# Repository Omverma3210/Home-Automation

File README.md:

# Home-Automation
A smart home automation switch based on triac

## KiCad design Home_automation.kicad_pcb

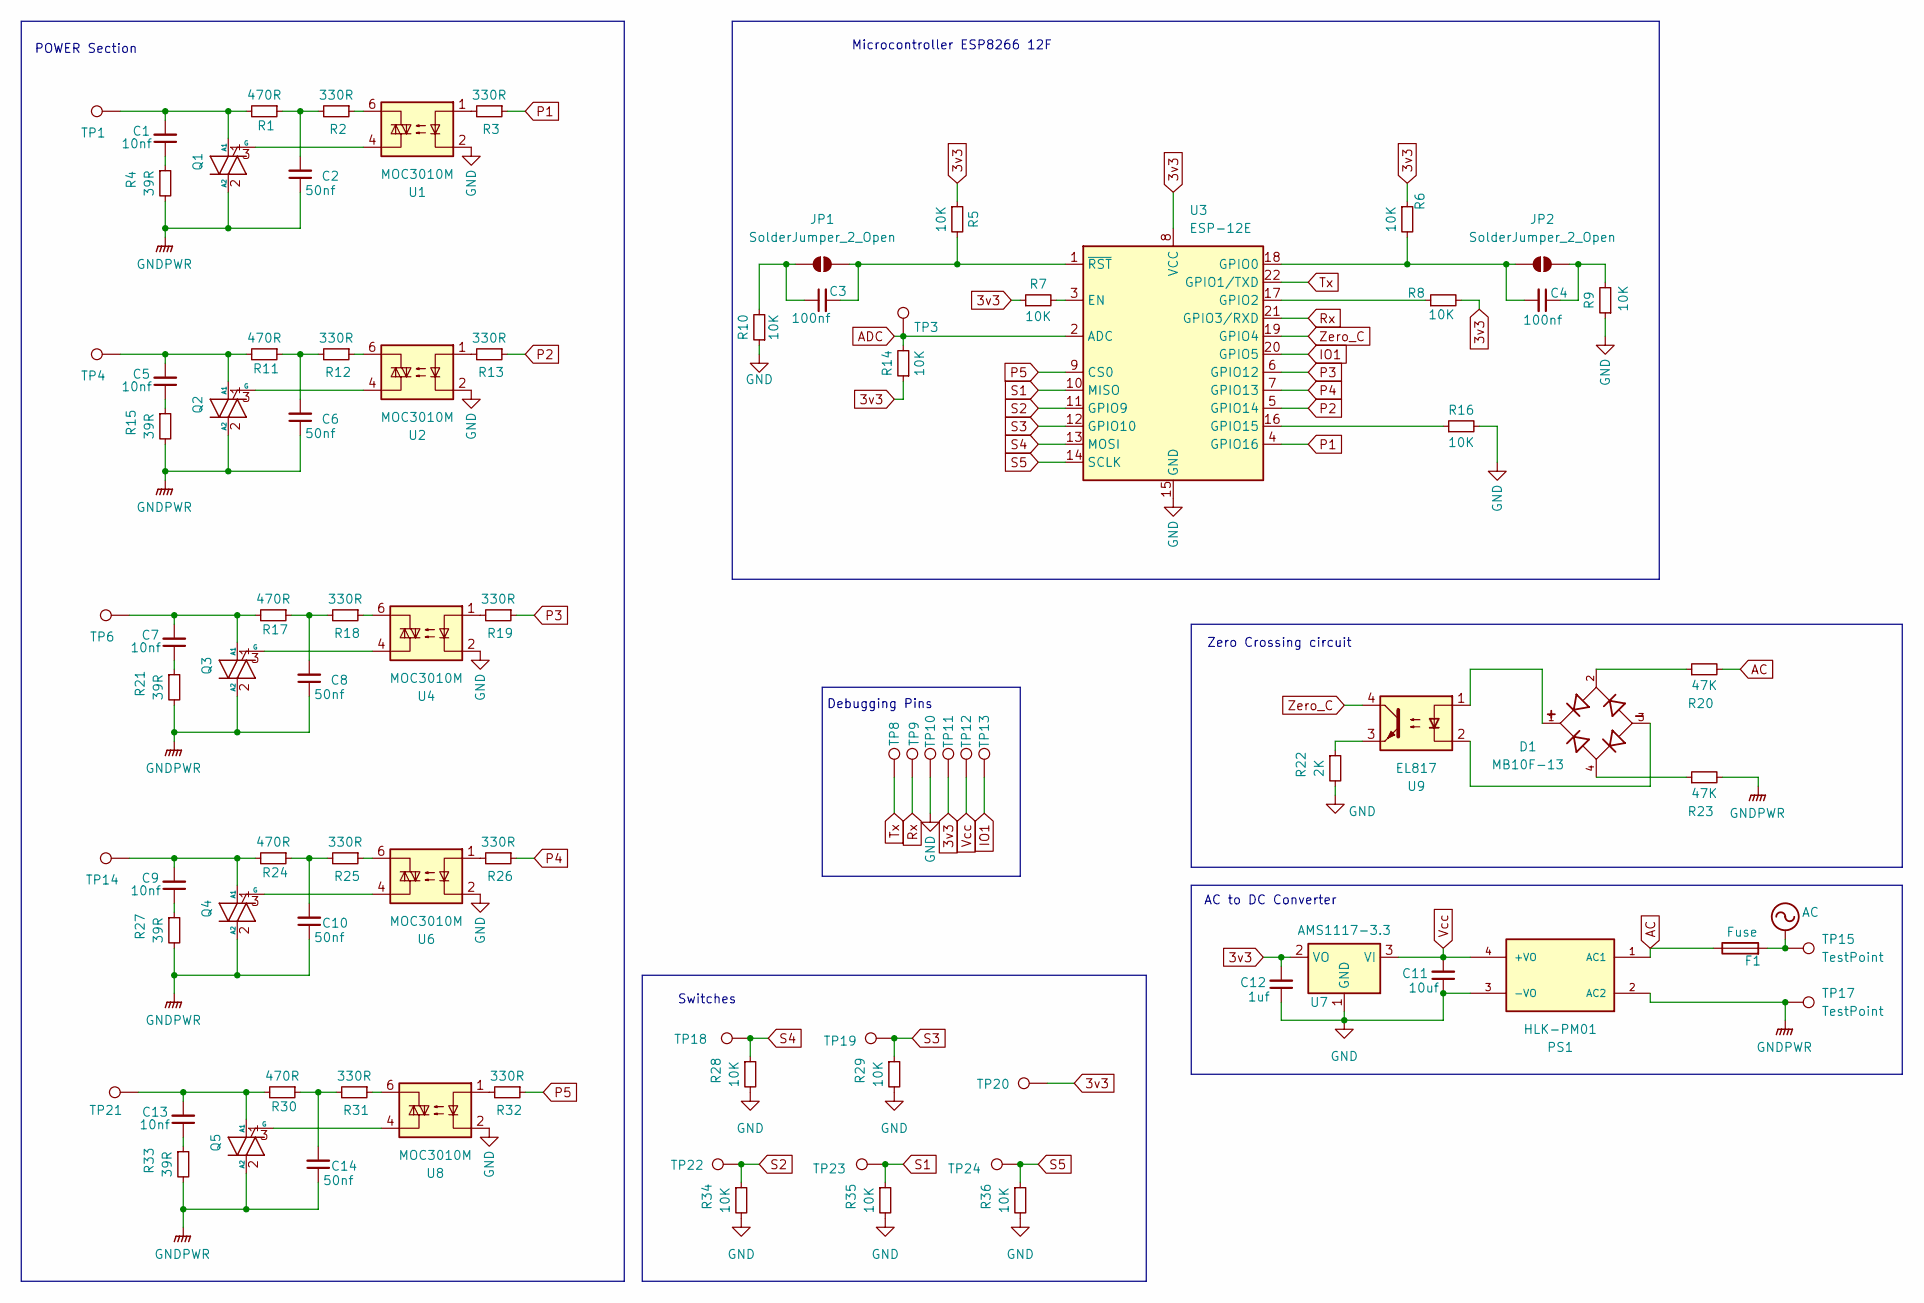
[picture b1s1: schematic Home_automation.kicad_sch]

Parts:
C1, C5, C7, C9, C13: 10nf; C_Rect_L13.0mm_W3.0mm_P10.00mm_FKS3_FKP3_MKS4
C2, C6, C8, C10, C14: 50nf; C_Rect_L13.0mm_W3.0mm_P10.00mm_FKS3_FKP3_MKS4
C3, C4: 100nf; C_0402_1005Metric_Pad0.74x0.62mm_HandSolder
C11: 10uf; C_0805_2012Metric
C12: 1uf; C_0603_1608Metric_Pad1.08x0.95mm_HandSolder
D1: MB10F-13; DIOB_MB10F-13; PARTREV 3 - 2
F1: Fuse; Fuseholder_Cylinder-5x20mm_Schurter_0031_8201_Horizontal_Op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
JP1, JP2: SolderJumper_2_Open; my_foot
PS1: HLK-PM01; CONV_HLK-PM01
Q1, Q2, Q3, Q4, Q5: BTA16-600B; TO-220-3_Vertical
R1, R11, R17, R24, R30: 470R; R_0603_1608Metric_Pad0.98x0.95mm_HandSolder
R2, R3, R12, R13, R18, R19, R25, R26, R31, R32: 330R; R_0603_1608Metric_Pad0.98x0.95mm_HandSolder
R4, R15, R21, R27, R33: 39R; R_0603_1608Metric_Pad0.98x0.95mm_HandSolder
R5, R6, R7, R8, R9, R10, R14, R16, R28, R29, R34, R35, R36: 10K; R_0603_1608Metric_Pad0.98x0.95mm_HandSolder
R20, R23: 47K; R_0603_1608Metric_Pad0.98x0.95mm_HandSolder
R22: 2K; R_0603_1608Metric_Pad0.98x0.95mm_HandSolder
TP1, TP4, TP6, TP14, TP15, TP17, TP21: TestPoint; TestPoint_Loop_D3.80mm_Drill2.0mm
TP3, TP8, TP9, TP10, TP11, TP12, TP13: TestPoint; TestPoint_Pad_1.0x1.0mm
TP18, TP19, TP20, TP22, TP23, TP24: TestPoint; TestPoint_THTPad_D2.0mm_Drill1.0mm
U1, U2, U4, U6, U8: MOC3010M; DIP-6_W7.62mm
U3: ESP-12E
U7: AMS1117-3.3; SOT-223-3_TabPin2
U9: EL817; DIP-4_W7.62mm

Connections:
3v3: C12.2, R5.1, R6.1, R7.1, R8.2, R14.1, TP11.1, TP20.1, U3.8 (VCC), U7.2 (VO)
AC: F1.1, F1.2, PS1.1 (AC1), R20.2, TP15.1; also elsewhere on the board
ADC: R14.2, TP3.1, U3.2 (ADC)
GND: C11.1, C12.1, PS1.3 (-VO), R9.1, R10.1, R16.2, R22.2, R28.2, R29.2, R34.2, R35.2, R36.2, TP10.1, U1.2, U2.2, U3.15 (GND), U4.2, U6.2, U7.1 (GND), U8.2
GNDPWR: C2.1, C6.1, C8.1, C10.1, C14.1, PS1.2 (AC2), Q1.2 (A2), Q2.2 (A2), Q3.2 (A2), Q4.2 (A2), Q5.2 (A2), R4.2, R15.2, R21.2, R23.2, R27.2, R33.2, TP17.1
IO1: TP13.1, U3.20 (GPIO5)
unnamed: C1.1, R4.1
unnamed: C2.2, R1.1, R2.2
unnamed: C5.1, R15.1
unnamed: C6.2, R11.1, R12.2
unnamed: C7.1, R21.1
unnamed: C8.2, R17.1, R18.2
unnamed: C9.1, R27.1
unnamed: C10.2, R24.1, R25.2
unnamed: C13.1, R33.1
unnamed: C14.2, R30.1, R31.2
unnamed: D1.1, U9.1
unnamed: D1.2, R20.1
unnamed: D1.3, U9.2
unnamed: D1.4, R23.1
unnamed: C3.1, JP1.1 (A), R10.2
unnamed: C3.2, JP1.2 (B), R5.2, U3.1 (~RST)
unnamed: C4.2, JP2.1 (A), R6.2, U3.18 (GPIO0)
unnamed: C4.1, JP2.2 (B), R9.2
unnamed: C1.2, Q1.1 (A1), R1.2, TP1.1
unnamed: Q1.3 (G), U1.4
unnamed: C5.2, Q2.1 (A1), R11.2, TP4.1
unnamed: Q2.3 (G), U2.4
unnamed: C7.2, Q3.1 (A1), R17.2, TP6.1
unnamed: Q3.3 (G), U4.4
unnamed: C9.2, Q4.1 (A1), R24.2, TP14.1
unnamed: Q4.3 (G), U6.4
unnamed: C13.2, Q5.1 (A1), R30.2, TP21.1
unnamed: Q5.3 (G), U8.4
unnamed: R2.1, U1.6
unnamed: R3.2, U1.1
unnamed: R12.1, U2.6
unnamed: R13.2, U2.1
unnamed: R18.1, U4.6
unnamed: R19.2, U4.1
unnamed: R22.1, U9.3
unnamed: R25.1, U6.6
unnamed: R26.2, U6.1
unnamed: R31.1, U8.6
unnamed: R32.2, U8.1
unnamed: R7.2, U3.3 (EN)
unnamed: R8.1, U3.17 (GPIO2)
unnamed: R16.1, U3.16 (GPIO15)
P1: R3.1, U3.4 (GPIO16)
P2: R13.1, U3.5 (GPIO14)
P3: R19.1, U3.6 (GPIO12)
P4: R26.1, U3.7 (GPIO13)
P5: R32.1, U3.9 (CS0)
Rx: TP9.1, U3.21 (GPIO3/RXD)
S1: R35.1, TP23.1, U3.10 (MISO)
S2: R34.1, TP22.1, U3.11 (GPIO9)
S3: R29.1, TP19.1, U3.12 (GPIO10)
S4: R28.1, TP18.1, U3.13 (MOSI)
S5: R36.1, TP24.1, U3.14 (SCLK)
Tx: TP8.1, U3.22 (GPIO1/TXD)
Vcc: C11.2, PS1.4 (+VO), TP12.1, U7.3 (VI)
Zero_C: U3.19 (GPIO4), U9.4

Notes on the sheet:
Switches
AC to DC Converter
Debugging Pins
POWER Section
Microcontroller ESP8266 12F
Zero Crossing circuit

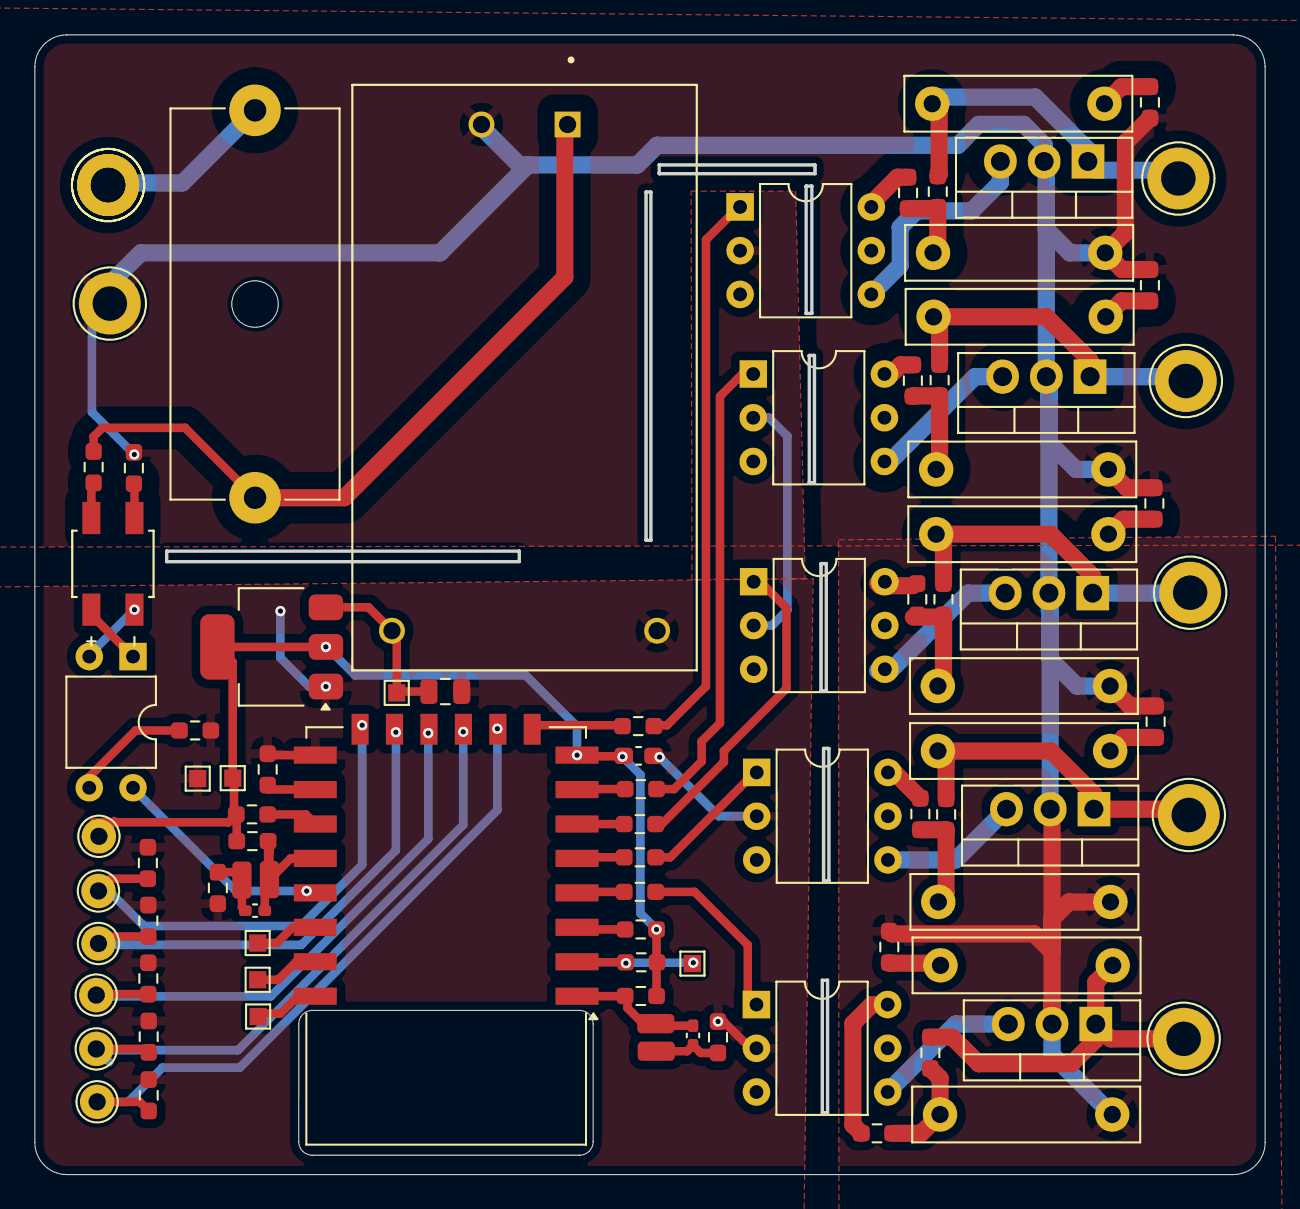
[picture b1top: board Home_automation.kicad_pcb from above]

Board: 2 copper layers, 71.3 x 66.0 mm, 89 parts (0 on the bottom side), 62 nets.

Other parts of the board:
TP26: TestPoint; TestPoint_Loop_D3.80mm_Drill2.0mm

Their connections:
AC: TP26.1; also elsewhere on the board

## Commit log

2024-09-14 updated pcb
2024-09-16 Add files via upload
    made pcb
